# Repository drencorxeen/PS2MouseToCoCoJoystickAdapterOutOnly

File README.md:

# PS2MouseToCoCoJoystickPortAdapterOutOnly
This project is design to take a PS/2 Mouse and convert it to be usable on a Tandy Radio Shack Color Computer's joystick port.

## Requirements
* 1x ATMega328P-PU chip DIP
* 1x Optional .300" wide 2.54mm pin spaced 28PIN Machine Socket Gold Plated
* 1x MCP4922 DIP
* 1x Optional .300" wide 2.54mm pin spaced 14PIN Machine Socket Gold Plated
* 1x 16MHz or 18.4323MHz crystal(If using 18.432MHz Crystal you will need MiniCore)
* 2x 1N4148 Diones
* 1x 10KΩ Resistor
* 2x 4.7KΩ Resistors
* 2x 470Ω Resistors
* 2x 3mm LEDs
* 2x 0.1µF Ceramic Capacitors
* 2x 22pF Ceramic Capacitors
* 1x MAB6H 6PIN DIN PCB Jack
* 1x mini B female USB connector THT PCB style (for receiving external +5V power)
* 1x 6PIN mini DIN female connector THT PCB style (for connecting PS/2 mouse)

You will also need the PS2Mouse Arduino library by Jacek Kunicki on Github:
https://github.com/rucek/arduino-ps2-mouse

You will also need the MCP49xx Arduino library by Thomas Backman on Github:
https://github.com/exscape/electronics/tree/master/Arduino/Libraries/DAC_MCP49xx

## Disclaimer

As with all DIY electronics projects, this project comes with absolutely no warranty and will not be held liable for any loss or damage caused to your Arduino or vintage PC you used this adapter on. Use at your own risk!

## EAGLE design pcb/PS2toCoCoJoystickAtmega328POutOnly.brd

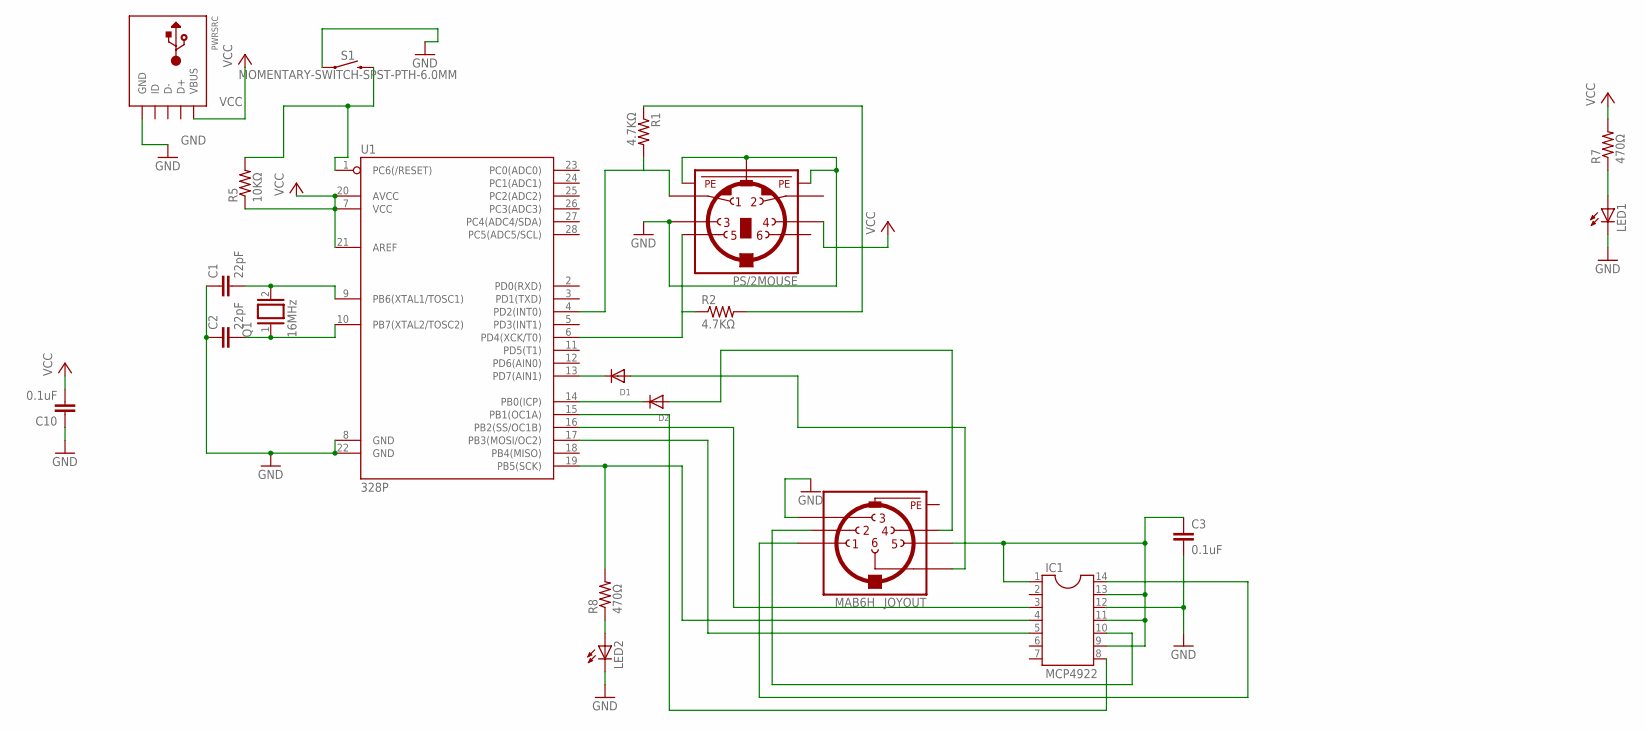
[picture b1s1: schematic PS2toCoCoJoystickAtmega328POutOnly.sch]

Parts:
C1, C2: 22pF; C2.5-3
C3, C10: 0.1uF; C5B2.5
D1, D2: DIODEDO-1N4148; DO-1N4148
IC1: MCP4922; DIL14
JOYOUT: MAB6H
LED1, LED2: LED3MM
PS/2MOUSE: MINI_DIN_6; M_DIN6
PWRSRC: USBTHM; USB-MINIB-THM
Q1: 16MHz; QS
R1, R2: 4.7KΩ; 0204/7
R5: 10KΩ; 0204/7
R7, R8: 470Ω; 0204/7
S1: MOMENTARY-SWITCH-SPST-PTH-6.0MM; TACTILE_SWITCH_PTH_6.0MM
U1: 328P; DIP28

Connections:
GND: C1.1, C2.1, C3.2, C10.1, IC1.12, JOYOUT.3, JOYOUT.PE, JOYOUT.PE@ (PE), LED1.K (C), LED2.K (C), PS/2MOUSE.3, PS/2MOUSE.SH1 (PE1), PS/2MOUSE.SH2 (PE2), PS/2MOUSE.SH3 (PE3), PWRSRC.GND, S1.1, U1.8 (GND), U1.22 (GND)
unnamed: C1.2, Q1.2, U1.9 (PB6(XTAL1/TOSC1))
unnamed: C2.2, Q1.1, U1.10 (PB7(XTAL2/TOSC2))
unnamed: R5.2, S1.3 (2), U1.1 (PC6(/RESET))
unnamed: D2.A, JOYOUT.4
unnamed: D1.C, U1.13 (PD7(AIN1))
unnamed: D2.C, U1.14 (PB0(ICP))
unnamed: C3.1, IC1.1, IC1.9, IC1.11, IC1.13, JOYOUT.5
unnamed: IC1.3, U1.16 (PB2(SS/OC1B))
unnamed: D1.A, JOYOUT.6
unnamed: IC1.10, JOYOUT.2
unnamed: IC1.14, JOYOUT.1
unnamed: PS/2MOUSE.1, R1.2, U1.4 (PD2(INT0))
unnamed: PS/2MOUSE.6 (5), R2.1, U1.6 (PD4(XCK/T0))
unnamed: IC1.8, U1.15 (PB1(OC1A))
unnamed: IC1.4, R8.2, U1.19 (PB5(SCK))
unnamed: IC1.5, U1.17 (PB3(MOSI/OC2))
unnamed: LED1.A, R7.1
unnamed: LED2.A, R8.1
VCC: C10.2, PS/2MOUSE.5 (4), PWRSRC.VBUS, R1.1, R2.2, R5.1, R7.2, U1.7 (VCC), U1.20 (AVCC), U1.21 (AREF)

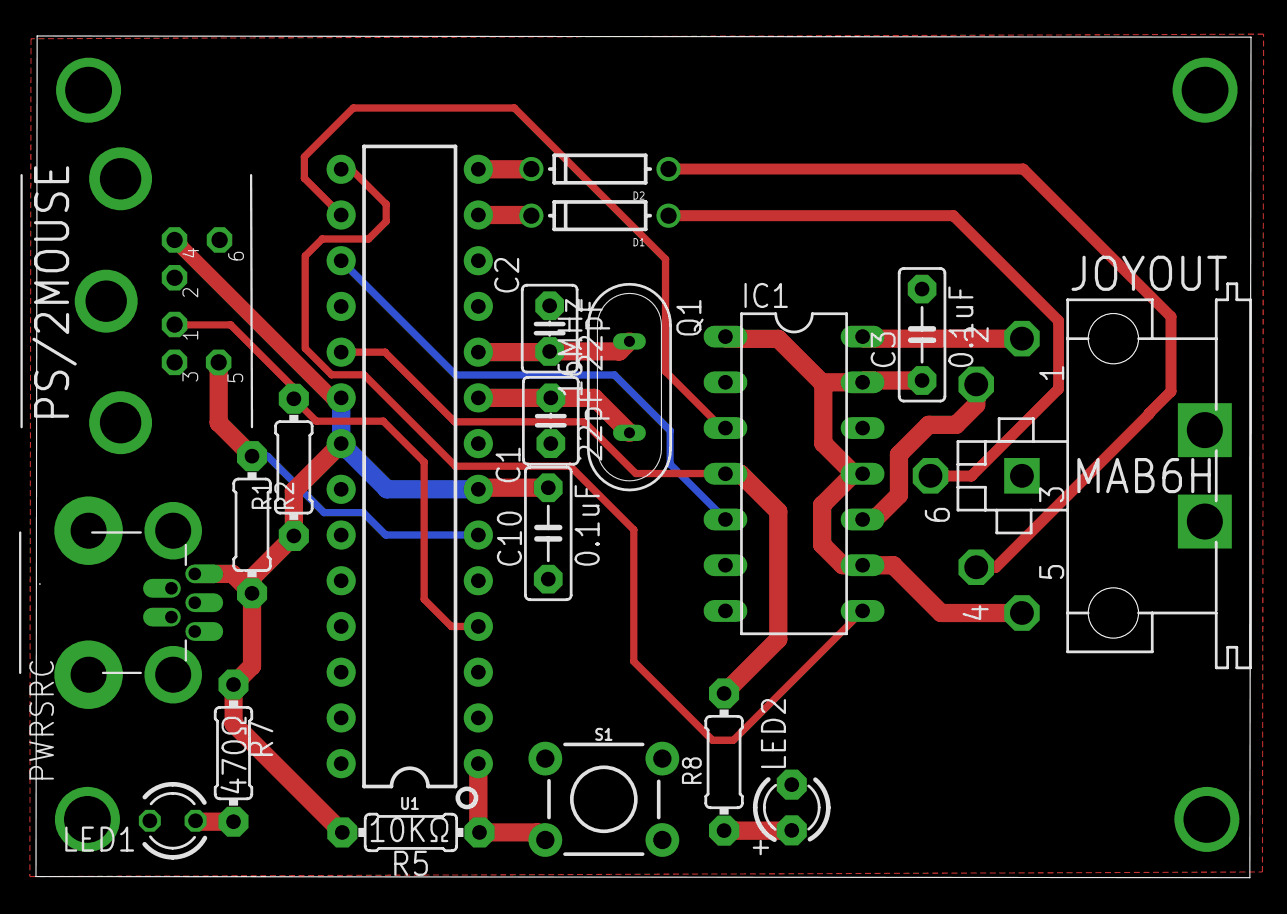
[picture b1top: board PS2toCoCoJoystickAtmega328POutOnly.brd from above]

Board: 2 copper layers, 67.5 x 46.8 mm, 20 parts (0 on the bottom side), 20 nets.

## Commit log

2020-04-04 Added ino file into repo for the code needed to run the project.
2020-04-04 Added the schematic and pcb files for the project.
2020-04-04 Added version.txt file to the repo and set v0.0.1a tag.
2020-04-05 Updated README.md to reflect parts list and where to get Arduino Libraries required to build the firmware.
2020-04-05 Updated Arduino sketch file to remove ifdef's based on AVR since MiniCore doesn't seem to set this. This change was needed as some PS/2 mice have slow µCU's that don't always come up in time for the 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

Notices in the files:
parts and their libraries:
SparkFun-IC-Microcontroller: Licensing: Creative Commons ShareAlike 4.0 International - https://creativecommons.org/licenses/by-sa/4.0
